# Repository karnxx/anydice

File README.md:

# Anydice
so this is a dice which can basically roll any number, it uses a xiao esp32c3, an oled, mpu 6040. u can set the max dice roll possibility and then shake and roll it like normal to produce a randomly generated number.

i made this project as my dnd dices wud get lost alot, and it couldnt roll some numbers, and using traditional rng online is distracting.

# WORKING
- so with the button you can set the max digit to roll. then u can shake the dice and actually roll it(mpu6050) to produce a final number on the oled, which is a random number between 0 and tht max digit. 

# PCB
- custom pcb via kicad, files [here](https://github.com/karnxx/anydice/tree/main/pcb)
- the pcb is mounted in the dice via screws, and the oled is mounted on the pcb with screws and spacers.

# [CAD](https://gmail4855044.autodesk360.com/g/shares/SH90d2dQT28d5b602811d05a79f94586e235)
- cadded via fusion360, files [here](https://github.com/karnxx/anydice/tree/main/cad)

# BOM
- bom is [here](https://docs.google.com/spreadsheets/d/12x69VHwHTzA7m8ty_oVYzZqYExIBdv50qRqhHhF5CHE/edit?usp=sharing)

| Part | Qty | Cost (₹) | Link |
|------|-----:|---------:|------|
| xiaoesp32c3 | 1 | 146.00 | https://robocraze.com/products/esp32-c3-mini-development-board-unsoldered |
| mpu6040 | 1 | 154.00 | https://robocraze.com/products/mpu-6050-triple-axis-accelerometer-gyroscope-module |
| right angle tactile pushbutton | 1 | 10.00 | https://probots.co.in/mini-push-switch-right-angled.html |
| tp4056 battery management | 1 | 36.00 | https://evelta.com/tp4056x-42-esop8-lithium-ion-battery-management-1a-ic-sop-8-ep/ |
| 250mah 3.7v li-ion | 1 | 126.00 | https://probots.co.in/3-7v-250mah-lipo-battery-502030-open-ended.html |
| capacitor 470uF | 1 | 5.00 | https://quartzcomponents.com/products/470-%C2%B5f-25v-radial-electrolytic-capacitor-through-hole |
| schottky diode | 4 | 3.00 | https://quartzcomponents.com/products/1n5819-shottky-barrier-diode |
| capacitor 0.1uF | 2 | 20.00 | https://quartzcomponents.com/products/10000-pf-0-1uf-ceramic-capacitor |
| resistor 4.7kΩ | 1 | 6.00 | https://quartzcomponents.com/products/4-7k-ohm-1-4-watt-resistor |
| OLED 1.3" 128×64 | 1 | 270.00 | https://robocraze.com/products/1-3in-oled-display |
| PCB | 1 | 1022.61 | — |
| **Total** |  | **1798.61** |  |

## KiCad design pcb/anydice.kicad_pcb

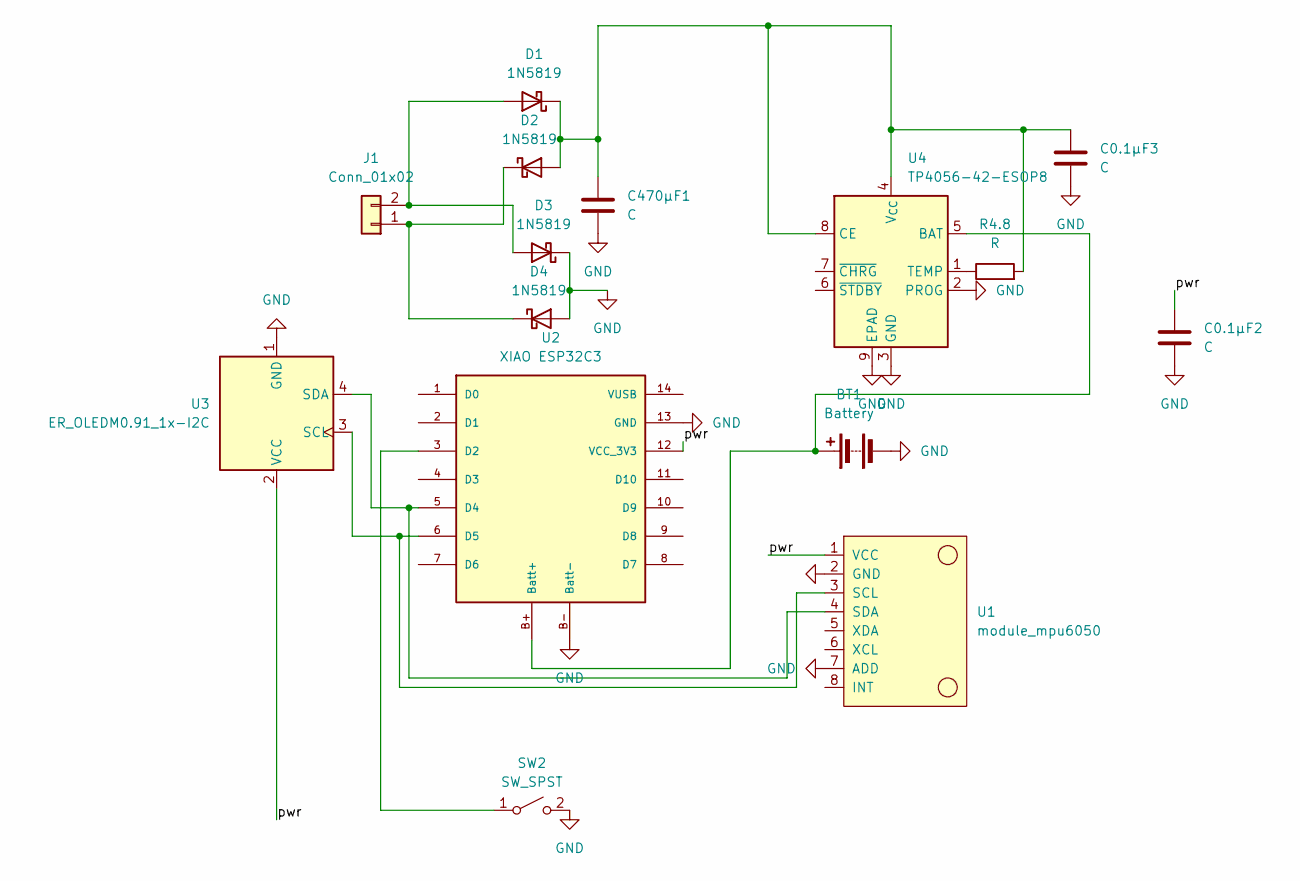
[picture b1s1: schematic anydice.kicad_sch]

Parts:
BT1: Battery; PinHeader_1x02_P2.54mm_Vertical
C0.1µF2, C0.1µF3: C; C_Disc_D3.0mm_W1.6mm_P2.50mm
C470µF1: C; CP_Radial_D8.0mm_P3.50mm
D1, D2, D3, D4: 1N5819; D_DO-41_SOD81_P10.16mm_Horizontal
J1: Conn_01x02; PinHeader_1x02_P2.54mm_Vertical
R4.8: R; R_Axial_DIN0207_L6.3mm_D2.5mm_P7.62mm_Horizontal
SW2: SW_SPST; SW_Tactile_SPST_Angled_PTS645Vx31-2LFS
U1: module_mpu6050
U2: XIAO ESP32C3; xiao_esp32c3
U3: ER_OLEDM0.91_1x-I2C
U4: TP4056-42-ESOP8; SOIC-8-1EP_3.9x4.9mm_P1.27mm_EP2.41x3.3mm

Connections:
/pwr: C0.1µF2.1, U1.1 (VCC), U2.12 (VCC_3V3), U3.2 (VCC)
GND: BT1.2 (-), C0.1µF2.2, C0.1µF3.2, C470µF1.2, D3.1 (K), D4.2 (A), SW2.2 (B), U1.2 (GND), U1.7 (ADD), U2.13 (GND), U2.B- (Batt-), U3.1 (GND), U4.2 (PROG), U4.3 (GND), U4.9 (EPAD)
unnamed: BT1.1 (+), U2.B+ (Batt+), U4.5 (BAT)
unnamed: D1.2 (A), D3.2 (A), J1.2
unnamed: C0.1µF3.1, C470µF1.1, D1.1 (K), D2.2 (A), R4.8.2, U4.4 (V_{CC}), U4.8 (CE)
unnamed: D2.1 (K), D4.1 (K), J1.1
unnamed: SW2.1 (A), U2.3 (D2)
unnamed: U1.3 (SCL), U2.6 (D5), U3.3 (SCL)
unnamed: U1.4 (SDA), U2.5 (D4), U3.4 (SDA)
unnamed: R4.8.1, U4.1 (TEMP)

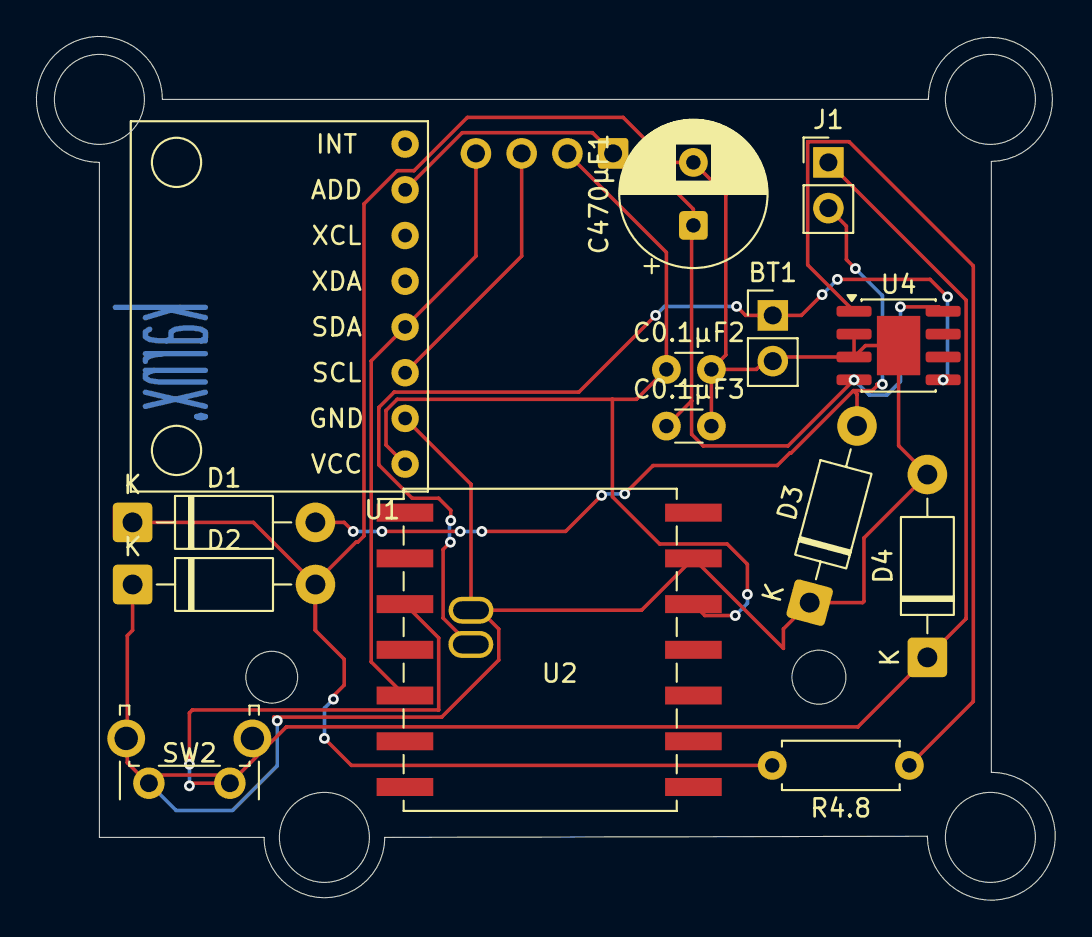
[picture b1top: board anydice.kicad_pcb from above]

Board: 2 copper layers, 56.6 x 48.0 mm, 15 parts (1 on the bottom side), 10 nets.

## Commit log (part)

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2026-06-04 added the pcb stuff
    production folder from kicad
2026-06-04 added more pcb parts
    added .kicak_pcb, prl, pro, sch.
2026-06-04 Create .step
    added step file of the pcb
2026-06-06 added add the files and cadfiles
2026-06-06 Rename anydice-journal.md to journal.md
2026-06-07 Add initial README for Anydice project
2026-06-07 Rename anydicebom - Sheet1.csv to anydicebom.csv
2026-06-15 added cads
2026-06-18 Rename anydice_firmware (2).ino to firmware.ino
